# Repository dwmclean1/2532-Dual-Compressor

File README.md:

# 2532-Dual-Compressor

## What is it?  

This is a dual mono clone of the Urei 1176LN compressor (2 x 1176 = 2532). The main board is a direct copy of the original unit from the original schematic. The ratio board is taken from the mnats version [seen here](http://mnats.net/1176_revision_d.html).  

The meter mode board was designed by me and uses two DPDT toggle switches, one to chose between displaying output level or gain reduction level and one to bypass the compression path. The Stereo Link board is also based on the mnats version which you would usually required two of but to save space and wiring I combined them into one board. All the boards were designed in EagleCAD.  

The original 1176 used two BF245 JFETs, one for the compression path and one for the gain reduction meter. These would need to matched so that the gain reduction shown on the meter is accurate to the actual gain reduction applied to the audio signal. Instead of doing that I decided to use the Interfet INF411 which is a matched pair of JFETs in a simgle package and has similar characteristics to the BF245.

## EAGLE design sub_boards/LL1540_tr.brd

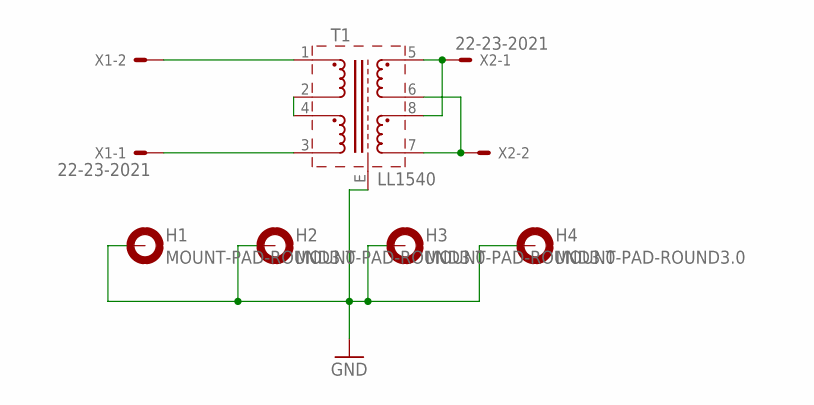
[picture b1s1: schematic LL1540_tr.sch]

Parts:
H1, H2, H3, H4: MOUNT-PAD-ROUND3.0; 3,0-PAD
T1: LL1540
X1, X2: 22-23-2021

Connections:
GND: H1.B3,0, H2.B3,0, H3.B3,0, H4.B3,0, T1.E
unnamed: T1.2, T1.4
unnamed: T1.1, X1.2
unnamed: T1.3, X1.1
unnamed: T1.5, T1.8, X2.1
unnamed: T1.6, T1.7, X2.2

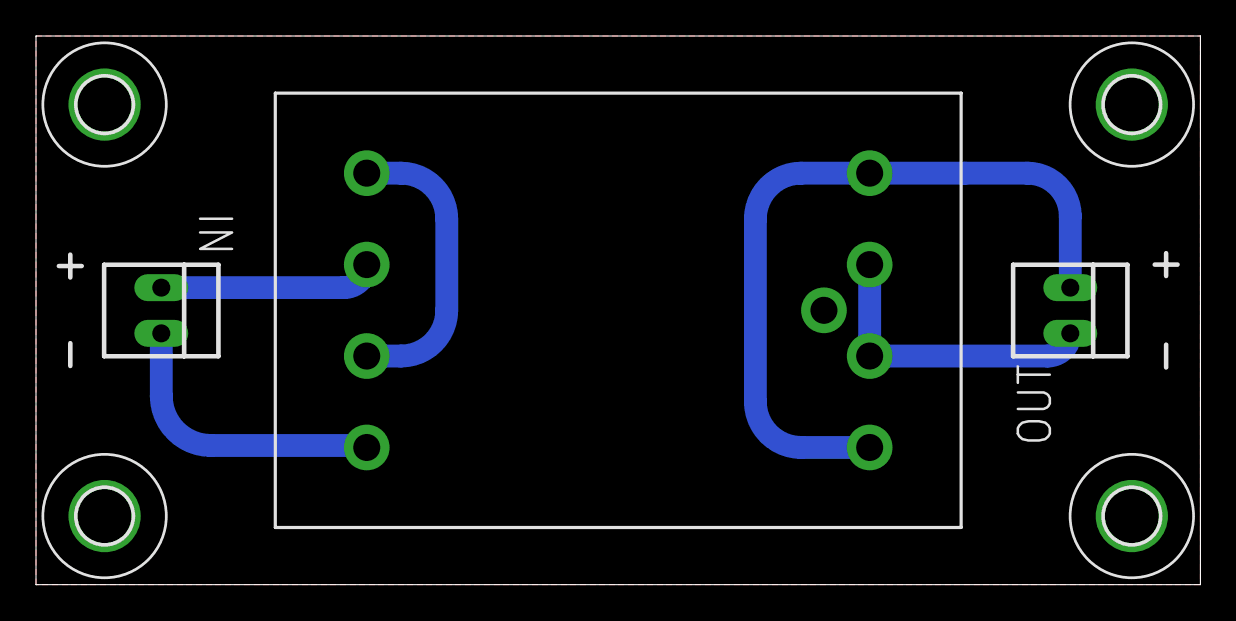
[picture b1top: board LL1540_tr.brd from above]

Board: 2 copper layers, 64.7 x 30.5 mm, 7 parts (0 on the bottom side), 6 nets.

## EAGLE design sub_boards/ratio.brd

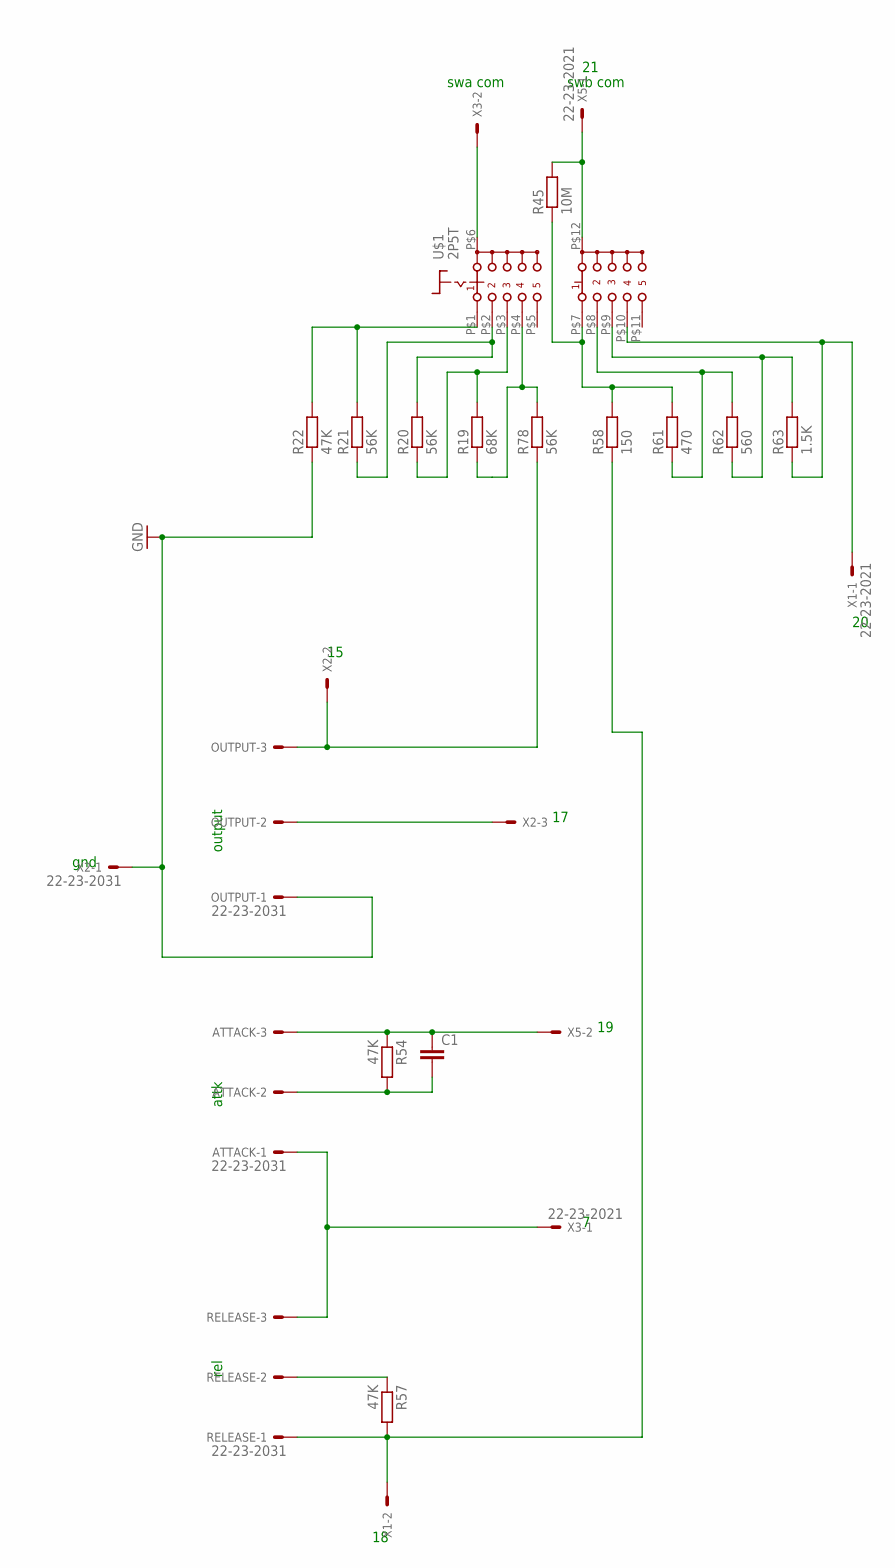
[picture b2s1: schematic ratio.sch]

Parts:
ATTACK: 22-23-2031
C1: C-EU025-025X050; C025-025X050
OUTPUT: 22-23-2031
R19: 68K; 0204V
R20, R21, R78: 56K; 0204V
R22, R54, R57: 47K; 0204V
R45: 10M; 0204V
R58: 150; 0204V
R61: 470; 0204V
R62: 560; 0204V
R63: 1.5K; 0204V
RELEASE: 22-23-2031
U$1: 2P5T
X1, X3, X5: 22-23-2021
X2: 22-23-2031

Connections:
GND: OUTPUT.1, R22.1, X2.1
unnamed: U$1.P$6 (A), X3.2
unnamed: R45.2, U$1.P$12 (C), X5.1
unnamed: R21.2, R22.2, U$1.P$1 (A1)
unnamed: R20.2, R21.1, U$1.P$2 (A2)
unnamed: R19.2, R20.1, U$1.P$3 (A3)
unnamed: R19.1, R78.2, U$1.P$4 (A4)
unnamed: OUTPUT.3, R78.1, X2.2
unnamed: R45.1, R58.2, R61.2, U$1.P$7 (C1)
unnamed: OUTPUT.2, X2.3
unnamed: ATTACK.3, C1.1, R54.1, X5.2
unnamed: R61.1, R62.2, U$1.P$8 (C2)
unnamed: R62.1, R63.2, U$1.P$9 (C3)
unnamed: R63.1, U$1.P$10 (C4), X1.1
unnamed: ATTACK.2, C1.2, R54.2
unnamed: ATTACK.1, RELEASE.3, X3.1
unnamed: R57.1, RELEASE.2
unnamed: R57.2, R58.1, RELEASE.1, X1.2

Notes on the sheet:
swa com
swb com
gnd
attk
rel
output

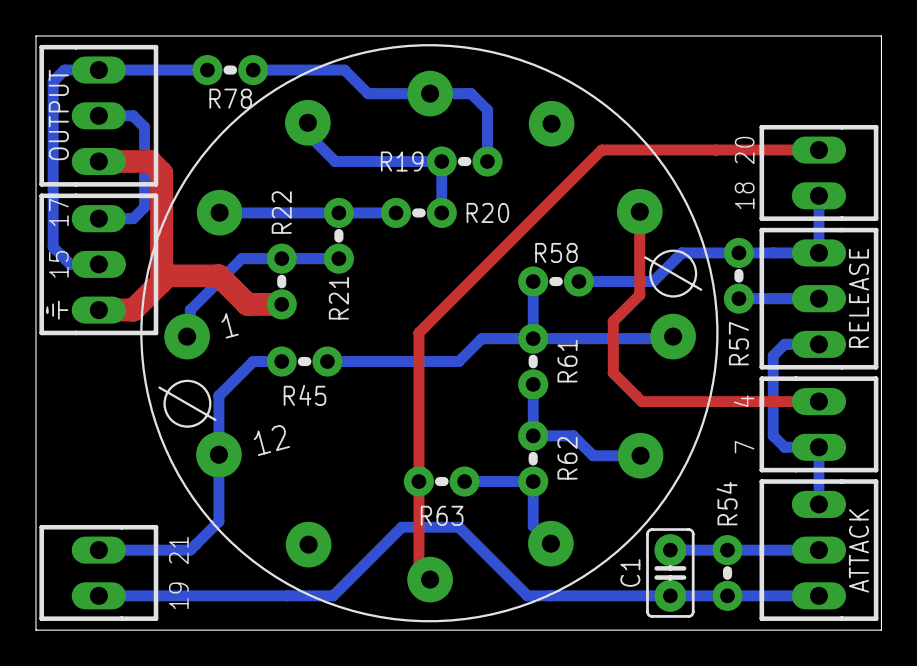
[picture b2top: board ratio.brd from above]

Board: 2 copper layers, 47.0 x 33.0 mm, 21 parts (0 on the bottom side), 18 nets.

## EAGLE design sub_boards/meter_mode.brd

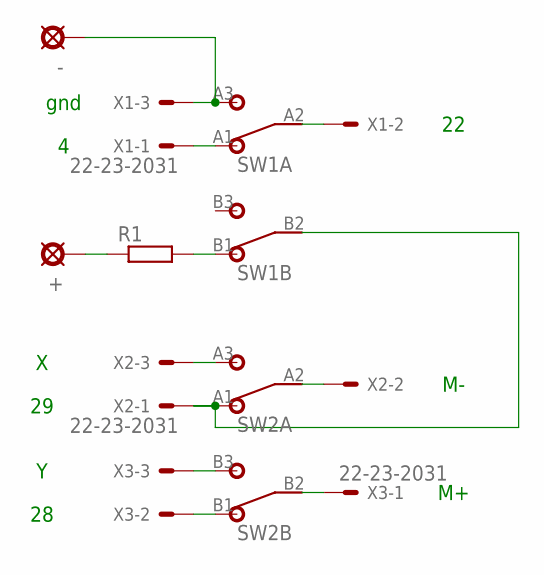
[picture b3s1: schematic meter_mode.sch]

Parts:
+: PADO; ROUND
-: PAD; SQUARE
R1: R-EU_0204/2V; 0204V
SW1, SW2: DPDT
X1, X2, X3: 22-23-2031

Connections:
unnamed: SW2.A3 (3), X2.3
unnamed: SW1.B2 (2), SW2.A1 (1), X2.1
unnamed: SW1.A1 (1), X1.1
unnamed: SW2.B3 (3), X3.3
unnamed: SW2.B1 (1), X3.2
unnamed: SW2.B2 (2), X3.1
unnamed: SW2.A2 (2), X2.2
unnamed: SW1.A2 (2), X1.2
unnamed: R1.2, SW1.B1 (1)
unnamed: -.1, SW1.A3 (3), X1.3
unnamed: +.1, R1.1

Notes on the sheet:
gnd

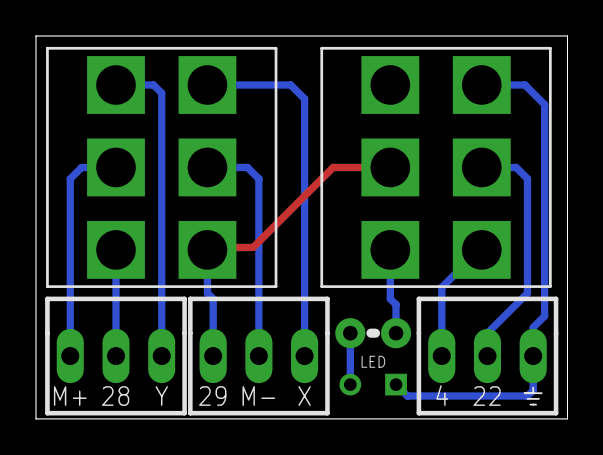
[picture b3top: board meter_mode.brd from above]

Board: 2 copper layers, 29.5 x 21.3 mm, 8 parts (0 on the bottom side), 11 nets.

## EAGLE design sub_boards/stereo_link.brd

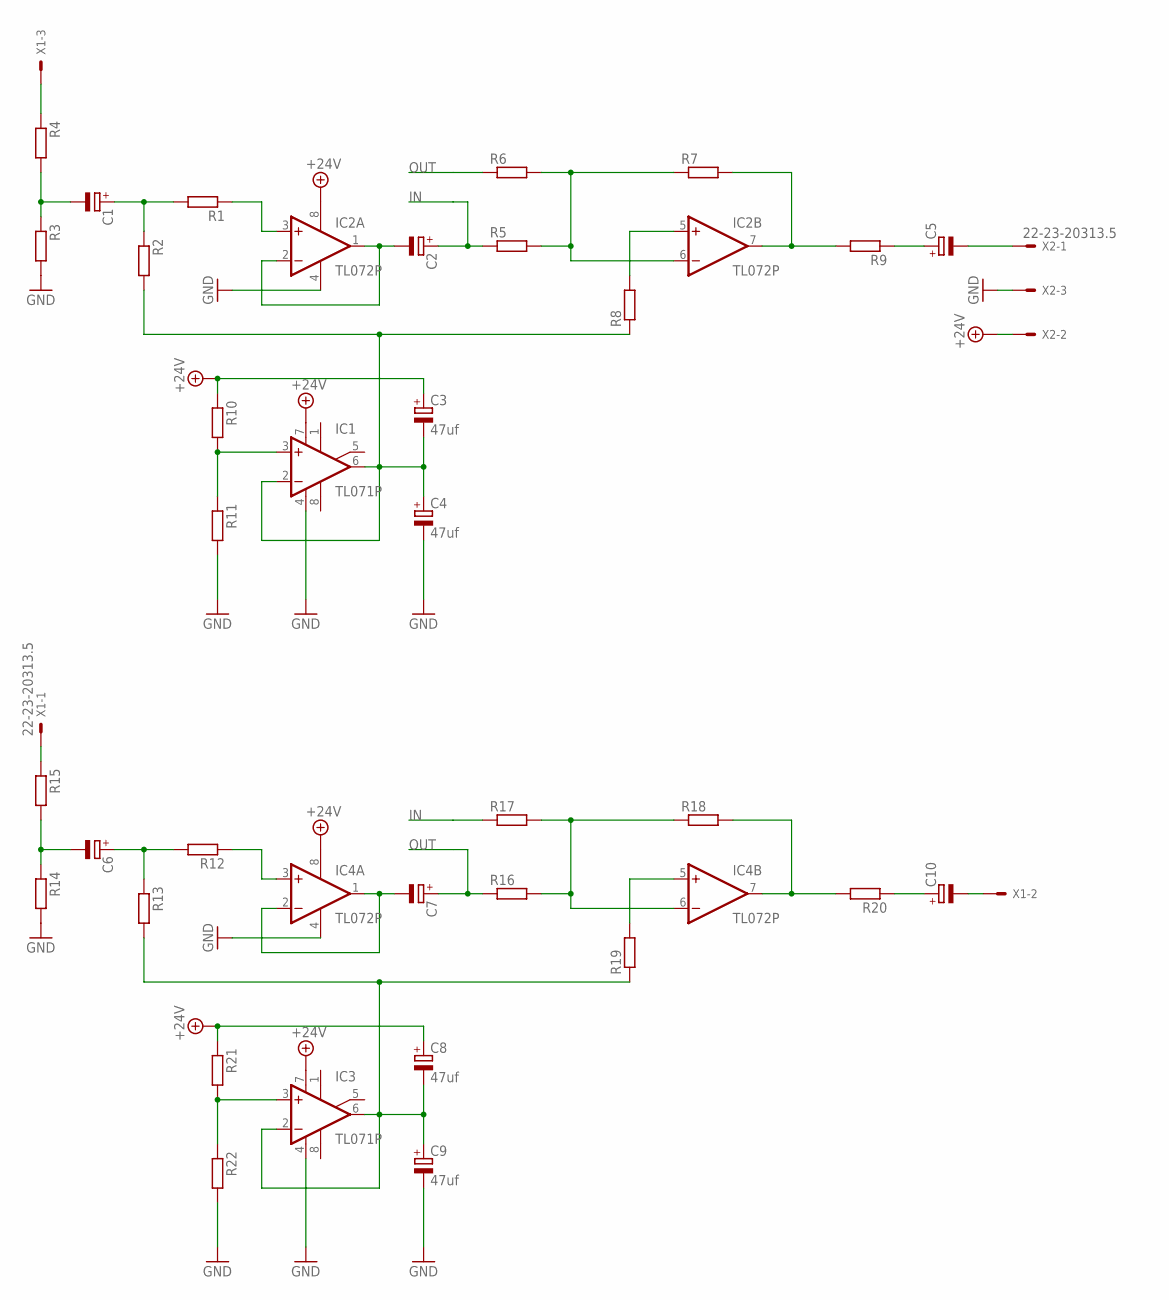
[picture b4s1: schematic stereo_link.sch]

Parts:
C1, C2, C5, C6, C7, C10: CPOL-EUE1.8-4; E1,8-4
C3, C4, C8, C9: 47uf; E2,5-6E
IC1, IC3: TL071P; DIL08
IC2, IC4: TL072P; DIL08
R1, R2, R3, R4, R5, R6, R7, R8, R9, R10, R11, R12, R13, R14, R15, R16, R17, R18, R19, R20, R21, R22: R-EU_0204/7; 0204/7
X1, X2: 22-23-20313.5; 3.5MM

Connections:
+24V: C3.+, C8.+, IC1.7 (V+), IC2.8 (V+), IC3.7 (V+), IC4.8 (V+), R10.1, R21.1, X2.P$2
GND: C4.-, C9.-, IC1.4 (V-), IC2.4 (V-), IC3.4 (V-), IC4.4 (V-), R3.2, R11.2, R14.2, R22.2, X2.P$3
unnamed: C1.-, R3.1, R4.2
unnamed: C1.+, R1.2, R2.1
unnamed: C6.-, R14.1, R15.2
unnamed: IC2.3 (+IN), R1.1
unnamed: C2.-, IC2.1 (OUT), IC2.2 (-IN)
unnamed: R15.1, X1.P$1
unnamed: C7.+, R6.1, R16.1
unnamed: IC2.6 (-IN), R5.2, R6.2, R7.1
unnamed: IC2.5 (+IN), R8.2
unnamed: IC2.7 (OUT), R7.2, R9.2
unnamed: C5.+, R9.1
unnamed: C5.-, X2.P$1
unnamed: IC1.3 (+IN), R10.2, R11.1
unnamed: C10.-, X1.P$2
unnamed: C6.+, R12.2, R13.1
unnamed: IC4.3 (+IN), R12.1
unnamed: C3.-, C4.+, IC1.2 (-IN), IC1.6 (OUT), R2.2, R8.1
unnamed: C7.-, IC4.1 (OUT), IC4.2 (-IN)
unnamed: R4.1, X1.P$3
unnamed: C2.+, R5.1, R17.1
unnamed: IC4.6 (-IN), R16.2, R17.2, R18.1
unnamed: IC4.5 (+IN), R19.2
unnamed: IC4.7 (OUT), R18.2, R20.2
unnamed: C10.+, R20.1
unnamed: IC3.3 (+IN), R21.2, R22.1
unnamed: C8.-, C9.+, IC3.2 (-IN), IC3.6 (OUT), R13.2, R19.1

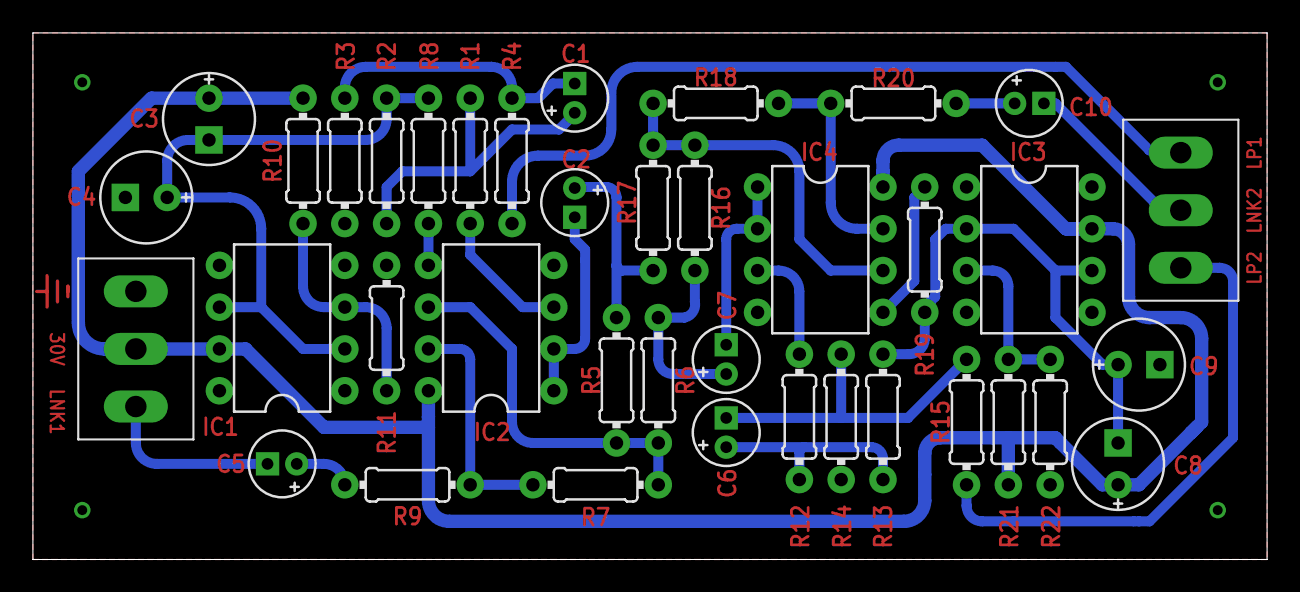
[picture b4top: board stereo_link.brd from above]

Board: 2 copper layers, 75.0 x 32.0 mm, 38 parts (0 on the bottom side), 28 nets.

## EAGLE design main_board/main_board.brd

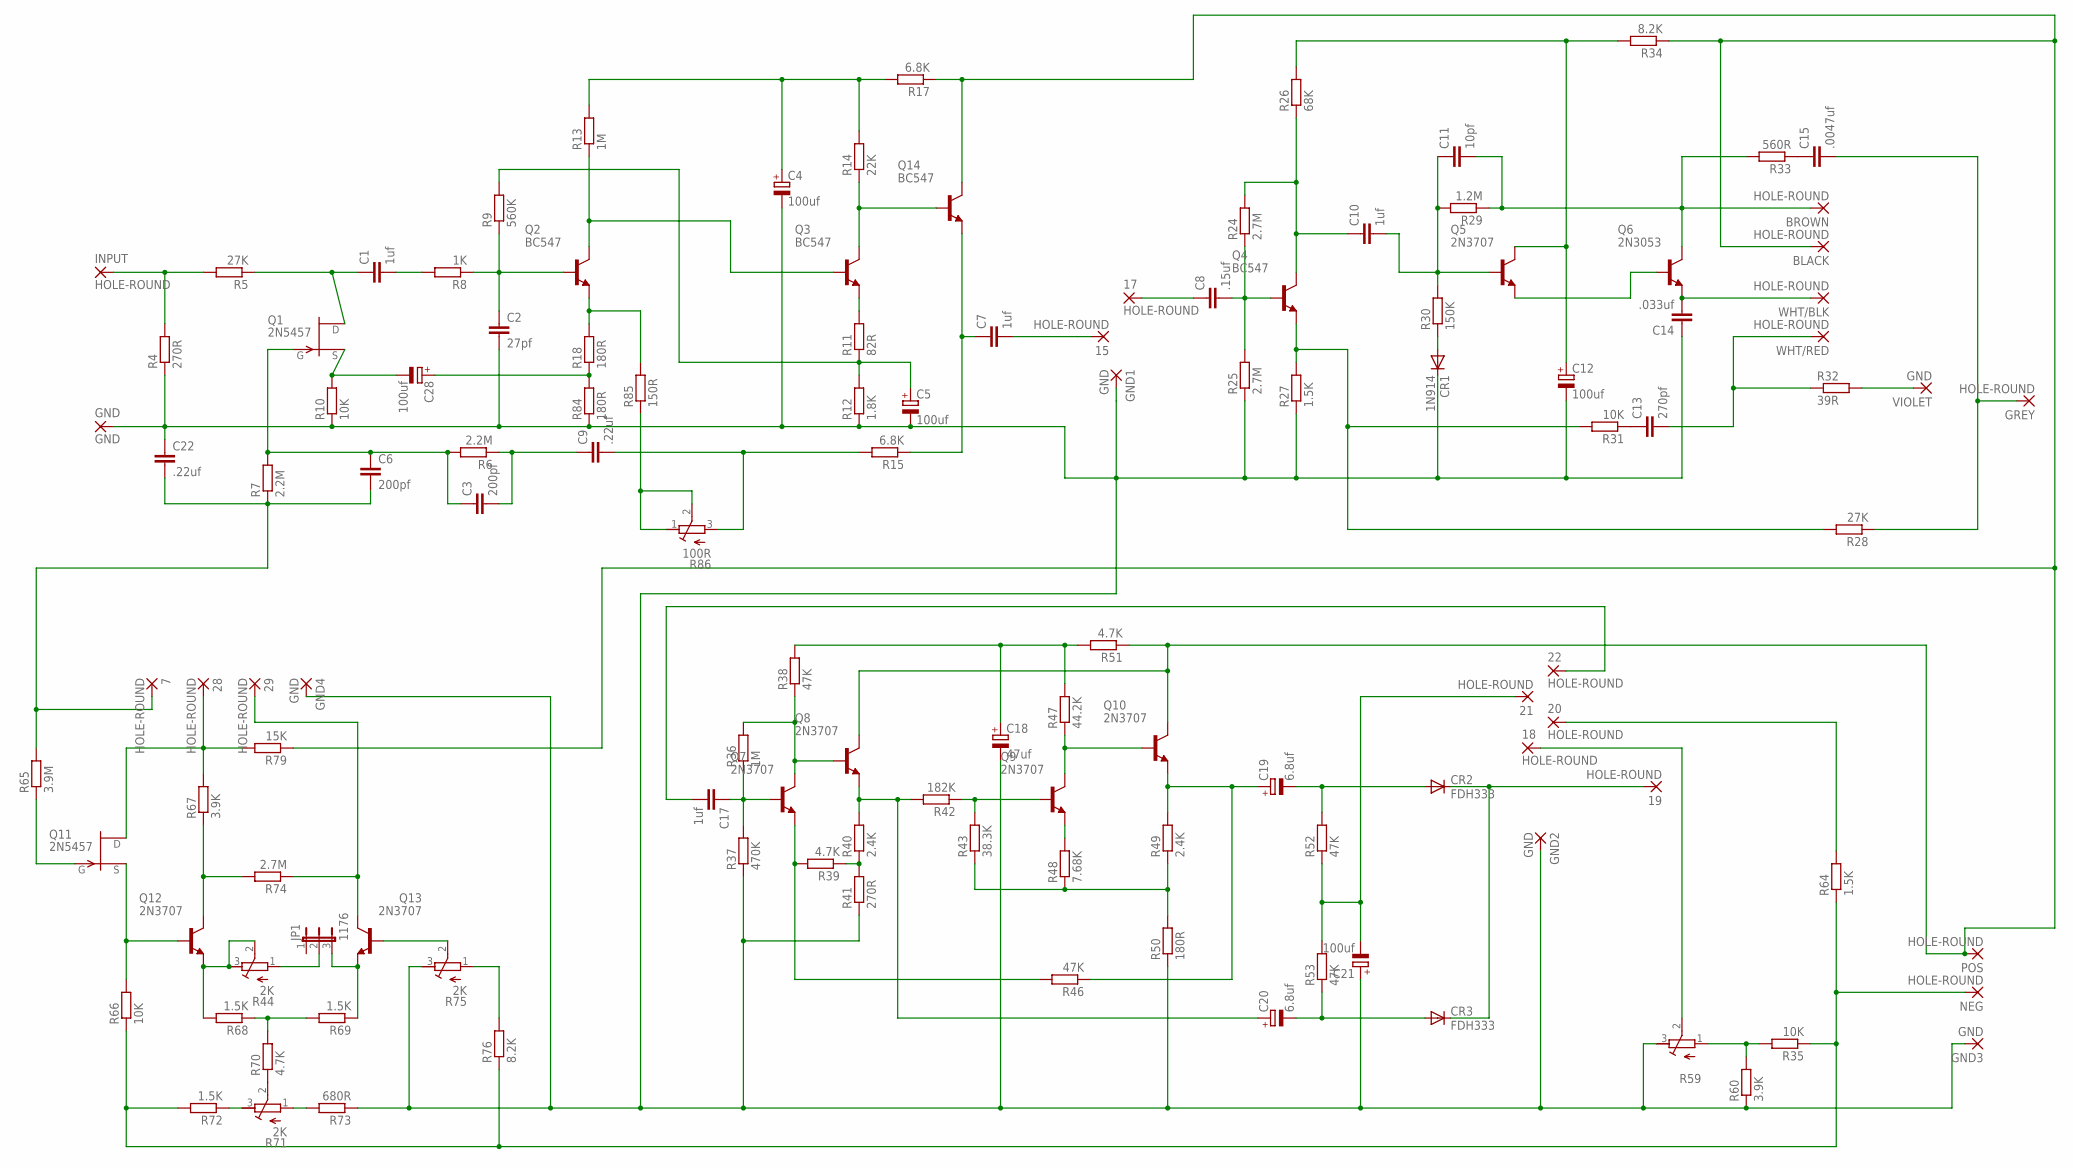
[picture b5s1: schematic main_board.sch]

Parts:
7, 15, 17, 18, 19, 20, 21, 22, 28, 29: HOLE-ROUND
BLACK: HOLE-ROUND
BROWN: HOLE-ROUND
C1, C7, C10, C17: 1uf; SQUARE
C2: 27pf; C-EU-ROUND
C3, C6: 200pf; C050-024X044
C4, C5, C12, C21, C28: 100uf; ROUND7
C8: .15uf; C-EU-ROUND
C9, C22: .22uf; C-EU-ROUND
C11: 10pf; C075-032X103
C13: 270pf; C-EU-ROUND
C14: .033uf; C-EU-ROUND
C15: .0047uf; C-EU-ROUND
C18: 47uf; E2,5-6
C19, C20: 6.8uf; E1,8-4
CR1: 1N914; DO41-10
CR2, CR3: FDH333; DO41-10
GND, GND1, GND2, GND3, GND4: GND; HOLE-SQUARE
GREY: HOLE-ROUND
INPUT: HOLE-ROUND
JP1: 1176
NEG: HOLE-ROUND
POS: HOLE-ROUND
Q1, Q11: 2N5457; TO92
Q2, Q3, Q4, Q14: BC547; TO92
Q5, Q7, Q8, Q9, Q10, Q12, Q13: 2N3707; TO92
Q6: 2N3053; TO39
R4: 270R; ROUND
R5, R28: 27K; ROUND
R6, R7: 2.2M; 0207/10
R8: 1K; 0207/10
R9: 560K; 0207/10
R10, R31, R35, R66: 10K; 0207/10
R11: 82R; ROUND
R12: 1.8K; ROUND
R13, R36: 1M; ROUND
R14: 22K; ROUND
R15, R17: 6.8K; 0207/10
R18, R50, R84: 180R; 0207/10
R24, R25, R74: 2.7M; ROUND
R26: 68K; ROUND
R27, R64, R68, R69, R72: 1.5K; ROUND
R29: 1.2M; ROUND
R30: 150K; 0207/10
R32: 39R; ROUND
R33: 560R; ROUND
R34, R76: 8.2K; 0207/10
R37: 470K; 0207/10
R38, R46, R52, R53: 47K; ROUND
R39, R51, R70: 4.7K; 0207/10
R40, R49: 2.4K; ROUND
R41: 270R; 0207/10
R42: 182K; ROUND
R43: 38.3K; ROUND
R44, R71, R75: 2K; RTRIM3296W
R47: 44.2K; ROUND
R48: 7.68K; ROUND
R59: R-TRIMM3296W; RTRIM3296W
R60, R67: 3.9K; ROUND
R65: 3.9M; ROUND
R73: 680R; 0207/10
R79: 15K; ROUND
R85: 150R; 0207/10
R86: 100R; RTRIM3339P
VIOLET: GND; HOLE-SQUARE
WHT/BLK: HOLE-ROUND
WHT/RED: HOLE-ROUND

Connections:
GND: C2.2, C4.-, C5.-, C12.-, C14.1, C18.-, C21.+, C22.1, CR1.C, GND.1, GND1.1, GND2.1, GND3.1, GND4.1, R4.P$1 (1), R10.1, R12.P$1 (1), R25.P$1 (1), R27.P$1 (1), R37.1, R41.1, R50.1, R59.3 (E), R60.P$1 (1), R73.1, R75.3 (E), R84.1
unnamed: 22.1, C17.2
unnamed: Q11.1 (G), R65.P$1 (1)
unnamed: 28.1, Q11.3 (D), R67.P$3 (2), R79.P$3 (2)
unnamed: Q11.2 (S), Q12.3 (B), R66.2
unnamed: NEG.1, R35.1, R64.P$1 (1), R66.1, R72.P$3 (2), R76.1
unnamed: R70.1, R71.2 (S)
unnamed: Q12.2 (C), R67.P$1 (1), R74.P$3 (2)
unnamed: R68.P$1 (1), R69.P$3 (2), R70.2
unnamed: Q12.1 (E), R44.2 (S), R44.3 (E), R68.P$3 (2)
unnamed: 20.1, R64.P$3 (2)
unnamed: JP1.3, Q13.1 (E), R69.P$1 (1)
unnamed: 29.1, Q13.2 (C), R74.P$1 (1)
unnamed: R71.3 (E), R72.P$1 (1)
unnamed: Q13.3 (B), R75.2 (S)
unnamed: Q3.1 (C), Q14.2 (B), R14.P$1 (1)
unnamed: R75.1 (A), R76.2
unnamed: INPUT.1, R4.P$3 (2), R5.P$3 (2)
unnamed: JP1.2, R44.1 (A)
unnamed: Q4.3 (E), R27.P$3 (2), R28.P$3 (2), R31.2
unnamed: R71.1 (A), R73.2
unnamed: C1.1, Q1.3 (D), R5.P$1 (1)
unnamed: C1.2, R8.2
unnamed: C3.1, C6.1, Q1.1 (G), R6.2, R7.2
unnamed: C28.-, Q1.2 (S), R10.2
unnamed: C13.2, R32.P$1 (1), WHT/RED.1
unnamed: C3.2, C9.1, R6.1
unnamed: C28.+, R18.1, R84.2
unnamed: 15.1, C7.2
unnamed: C2.1, Q2.2 (B), R8.1, R9.1
unnamed: C17.1, Q7.3 (B), R36.P$1 (1), R37.2
unnamed: Q2.3 (E), R18.2, R85.2
unnamed: C9.2, R15.2, R86.3 (A)
unnamed: R85.1, R86.1 (E), R86.2 (S)
unnamed: Q2.1 (C), Q3.2 (B), R13.P$1 (1)
unnamed: C5.+, R9.2, R11.P$1 (1), R12.P$3 (2)
unnamed: C4.+, R13.P$3 (2), R14.P$3 (2), R17.2
unnamed: Q5.1 (E), Q6.2 (B)
unnamed: Q3.3 (E), R11.P$3 (2)
unnamed: BROWN.1, C11.2, Q6.3 (C), R29.P$1 (1), R33.P$3 (2)
unnamed: C7.1, Q14.3 (E), R15.1
unnamed: R35.2, R59.1 (A), R60.P$3 (2)
unnamed: C15.2, GREY.1, R28.P$1 (1)
unnamed: Q7.2 (C), Q8.3 (B), R36.P$3 (2), R38.P$1 (1)
unnamed: 17.1, C8.1
unnamed: C8.2, Q4.2 (B), R24.P$1 (1), R25.P$3 (2)
unnamed: Q7.1 (E), R39.2, R46.P$3 (2)
unnamed: C10.1, Q4.1 (C), R24.P$3 (2), R26.P$1 (1)
unnamed: R39.1, R40.P$1 (1), R41.2
unnamed: C10.2, C11.1, Q5.3 (B), R29.P$3 (2), R30.2
unnamed: C20.-, CR3.A, R53.P$1 (1)
unnamed: CR1.A, R30.1
unnamed: C18.+, R38.P$3 (2), R47.P$3 (2), R51.2
unnamed: C12.+, Q5.2 (C), R26.P$3 (2), R34.2
unnamed: C13.1, R31.1
unnamed: C20.+, Q8.1 (E), R40.P$3 (2), R42.P$3 (2)
unnamed: BLACK.1, POS.1, Q8.2 (C), Q10.2 (C), Q14.1 (C), R17.1, R34.1, R51.1, R79.P$1 (1)
unnamed: Q9.3 (B), R42.P$1 (1), R43.P$3 (2)
unnamed: C15.1, R33.P$1 (1)
unnamed: R43.P$1 (1), R48.P$1 (1), R49.P$1 (1), R50.2
unnamed: Q9.1 (E), R48.P$3 (2)
unnamed: Q9.2 (C), Q10.3 (B), R47.P$1 (1)
unnamed: 19.1, CR2.C, CR3.C
unnamed: R32.P$3 (2), VIOLET.1
unnamed: C19.+, Q10.1 (E), R46.P$1 (1), R49.P$3 (2)
unnamed: 21.1, C21.-, R52.P$1 (1), R53.P$3 (2)
unnamed: 7.1, C6.2, C22.2, R7.1, R65.P$3 (2)
unnamed: C19.-, CR2.A, R52.P$3 (2)
unnamed: 18.1, R59.2 (S)
Q6: C14.2, Q6.1 (E), WHT/BLK.1

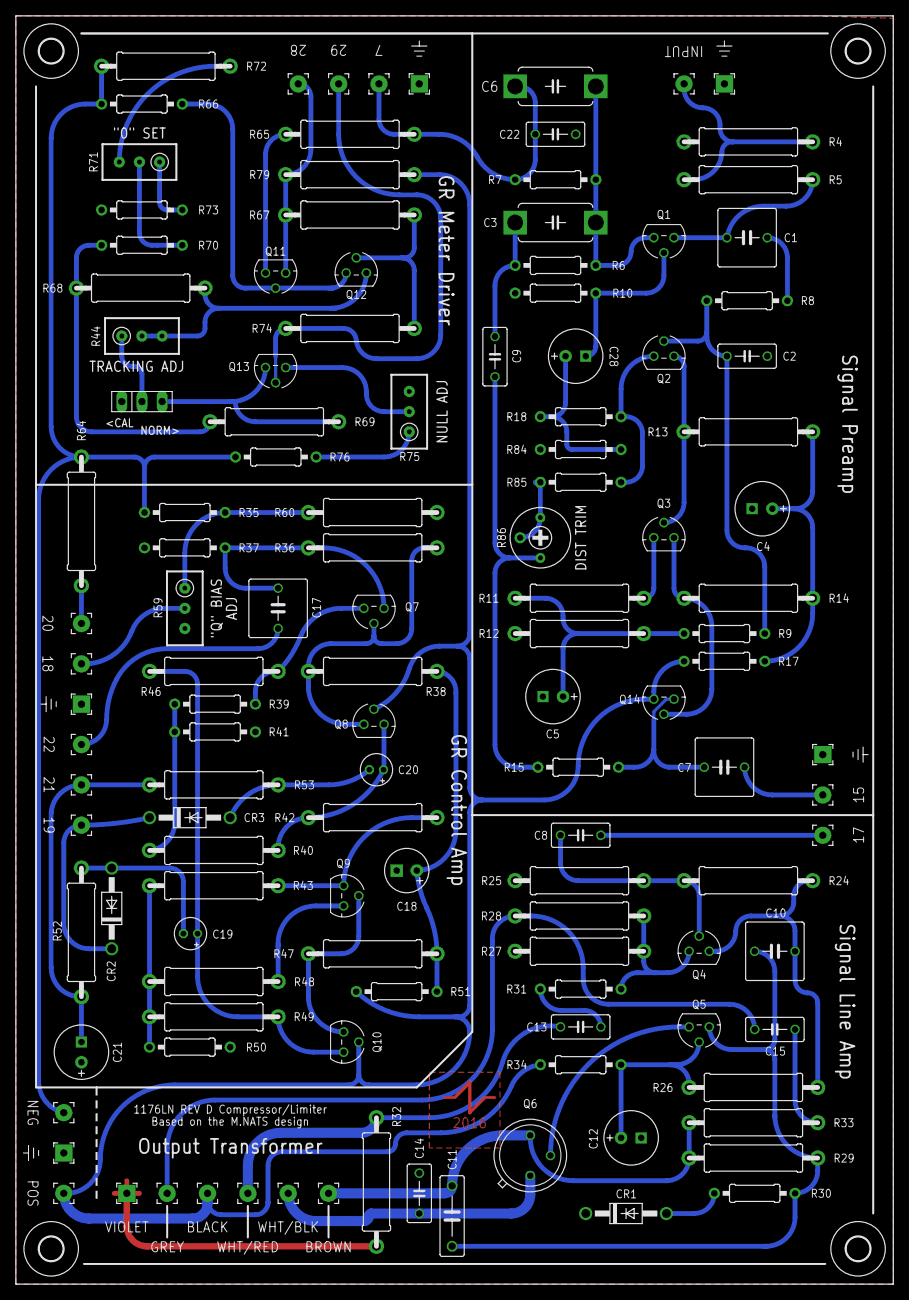
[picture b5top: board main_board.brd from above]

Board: 2 copper layers, 110.5 x 159.7 mm, 130 parts (0 on the bottom side), 70 nets.

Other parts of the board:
U$1, U$2, U$3, U$4: 3,0

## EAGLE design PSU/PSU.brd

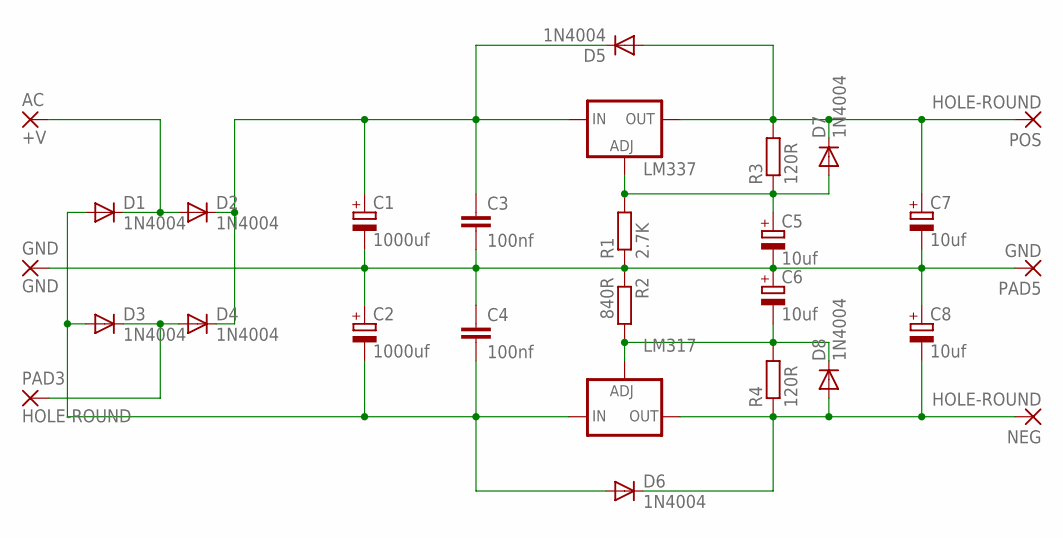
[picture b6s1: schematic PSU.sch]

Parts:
AC: +V; HOLE-ROUND
C1, C2: 1000uf; E3,5-10
C3, C4: 100nf; C025-025X050
C5, C6, C7, C8: 10uf; E2,5-5
D1, D2, D3, D4, D5, D6, D7, D8: 1N4004; DO41-10
GND: GND; HOLE-SQUARE
LM317: LM337TS; 337TS
LM337: LM317TS; 317TS
NEG: HOLE-ROUND
PAD3: HOLE-ROUND
PAD5: GND; HOLE-SQUARE
POS: HOLE-ROUND
R1: 2.7K; 0204/7
R2: 840R; 0204/7
R3, R4: 120R; 0204/7

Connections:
GND: C1.-, C2.+, C3.2, C4.1, C5.-, C6.+, C7.-, C8.+, GND.1, PAD5.1, R1.1, R2.1
unnamed: AC.1, D1.C, D2.A
unnamed: D3.C, D4.A, PAD3.1
unnamed: C6.-, D8.C, LM317.1 (ADJ), R2.2, R4.2
unnamed: C5.+, D7.A, LM337.1 (ADJ), R1.2, R3.1
unnamed: C8.-, D6.C, D8.A, LM317.3 (OUT), NEG.1, R4.1
unnamed: C1.+, C3.1, D2.C, D4.C, D5.C, LM337.3 (IN)
unnamed: C7.+, D5.A, D7.C, LM337.2 (OUT), POS.1, R3.2
unnamed: C2.-, C4.2, D1.A, D3.A, D6.A, LM317.2 (IN)

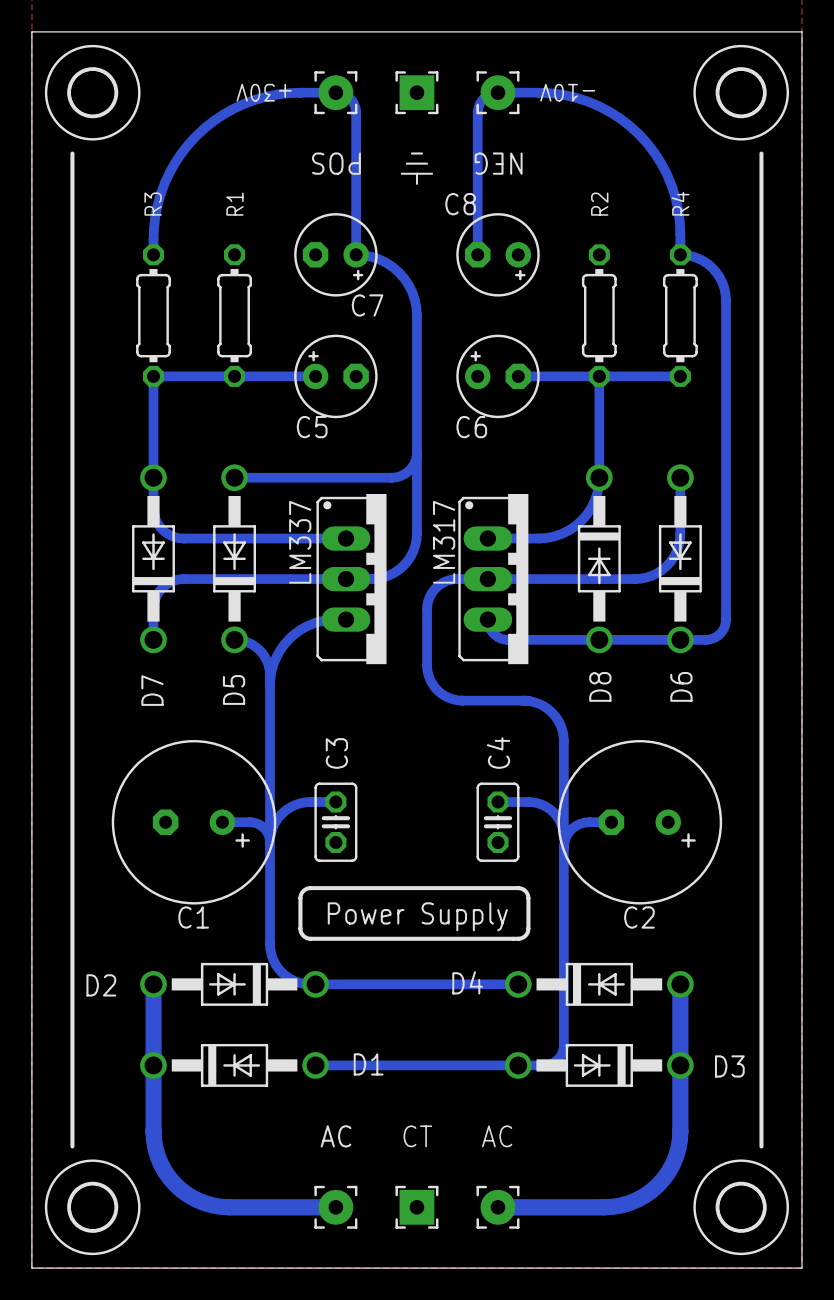
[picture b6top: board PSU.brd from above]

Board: 2 copper layers, 48.3 x 77.5 mm, 32 parts (0 on the bottom side), 9 nets.

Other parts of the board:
U$1, U$2, U$3, U$4: 2,8
